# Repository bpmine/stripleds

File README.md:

# stripleds
Projets pour bandeaux de LEDs

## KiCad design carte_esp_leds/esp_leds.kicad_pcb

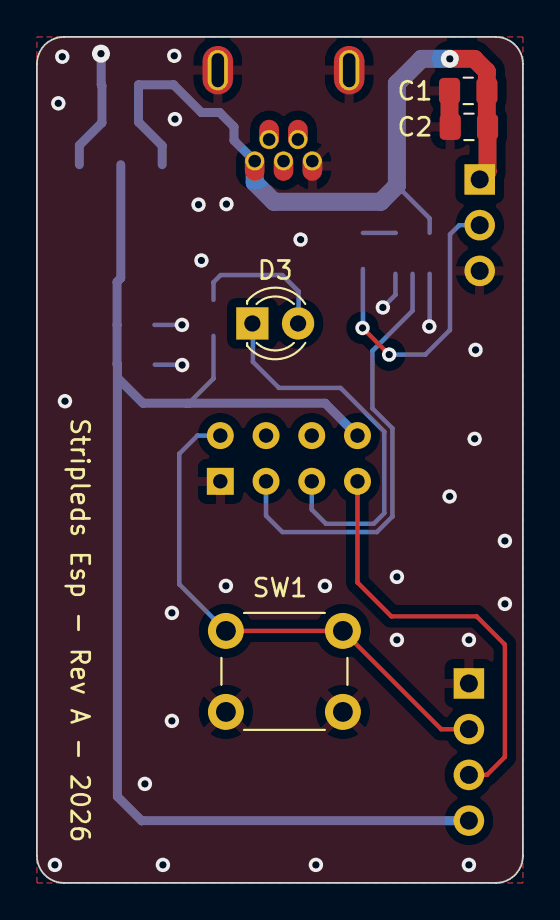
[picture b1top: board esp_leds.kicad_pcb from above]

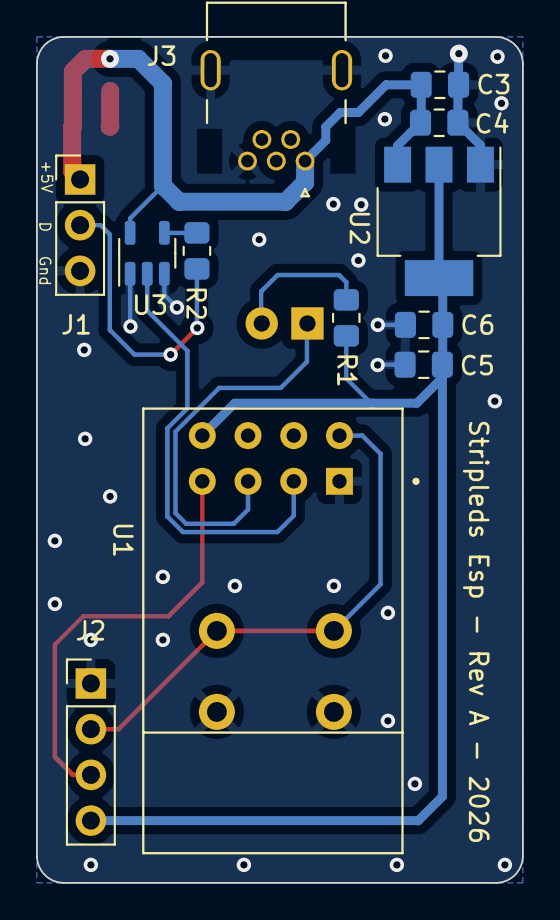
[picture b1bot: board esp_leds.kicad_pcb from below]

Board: 2 copper layers, 27.0 x 47.0 mm, 16 parts (12 on the bottom side), 10 nets.

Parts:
C1, C4, C6: 10n; C_0805_2012Metric_Pad1.18x1.45mm_HandSolder
C2, C3, C5: 1µF; C_0805_2012Metric_Pad1.18x1.45mm_HandSolder
D3: LED; LED_D3.0mm_FlatTop
J1: LEDs; PinHeader_1x03_P2.54mm_Vertical
J2: Prog; PinHeader_1x04_P2.54mm_Vertical
J3: 54819-0519; BPC_MiniUsb_Molex_54819-0519
R1: 220; R_0805_2012Metric_Pad1.20x1.40mm_HandSolder
R2: 100; R_0805_2012Metric_Pad1.20x1.40mm_HandSolder
SW1: SW_Push; SW_PUSH_6mm
U1: BPC_ESP8266-01_ESP-01; BPC_XCVR_ESP8266-01_ESP-01
U2: AMS1117-3.3; SOT-223-3_TabPin2
U3: 74AHCT1G125; SOT-23-5

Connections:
+3.3V: C5.2, C6.1, J2.4, R1.2, U1.8 (VCC), U2.2 (VO)
+5V: C1.2, C2.1, C3.2, C4.1, J1.1, J3.1 (VBUS), J3.6 (VBUS), U2.3 (VI), U3.5 (VCC)
DATA: U1.2 (IO2), U3.2
GND: C1.1, C2.2, C3.1, C4.2, C5.1, C6.2, J1.3, J2.1, J3.5 (GND), J3.10 (GND), J3.11 (SHIELD), J3.12 (SHIELD), J3.S1 (SHIELD), J3.S2 (SHIELD), SW1.2, U1.1 (GND), U2.1 (GND), U3.1, U3.3 (GND)
unnamed: D3.2 (A), R1.1
unnamed: D3.1 (K), U1.3 (IO0)
unnamed: J1.2, R2.1
unnamed: J2.2, SW1.1, U1.5 (TXD)
unnamed: J2.3, U1.4 (RXD)
unnamed: R2.2, U3.4

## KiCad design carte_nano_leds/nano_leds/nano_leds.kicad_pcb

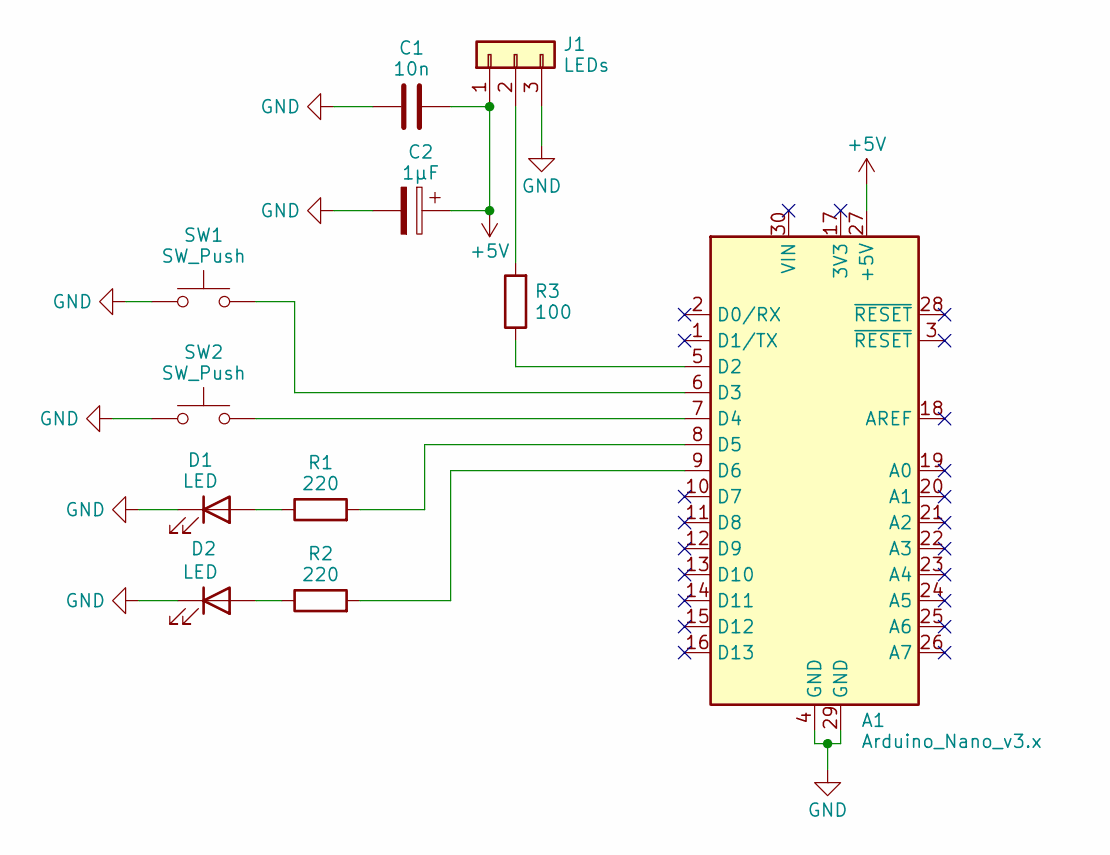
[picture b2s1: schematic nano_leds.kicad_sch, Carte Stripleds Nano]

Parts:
A1: Arduino_Nano_v3.x; BPC_Arduino_Nano
C1: 10n; C_0805_2012Metric_Pad1.18x1.45mm_HandSolder
C2: 1µF; C_0805_2012Metric_Pad1.18x1.45mm_HandSolder
D1, D2: LED; LED_D3.0mm_FlatTop
J1: LEDs; PinHeader_1x03_P2.54mm_Vertical
R1, R2: 220; R_0805_2012Metric_Pad1.20x1.40mm_HandSolder
R3: 100; R_0805_2012Metric_Pad1.20x1.40mm_HandSolder
SW1, SW2: SW_Push; SW_PUSH_6mm

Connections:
+5V: A1.27 (+5V), C1.2, C2.1, J1.1
GND: A1.4 (GND), A1.29 (GND), C1.1, C2.2, D1.1 (K), D2.1 (K), J1.3, SW1.1, SW2.1
unnamed: A1.5 (D2), R3.1
unnamed: A1.6 (D3), SW1.2
unnamed: A1.7 (D4), SW2.2
unnamed: A1.8 (D5), R1.2
unnamed: A1.9 (D6), R2.2
unnamed: D1.2 (A), R1.1
unnamed: D2.2 (A), R2.1
unnamed: J1.2, R3.2

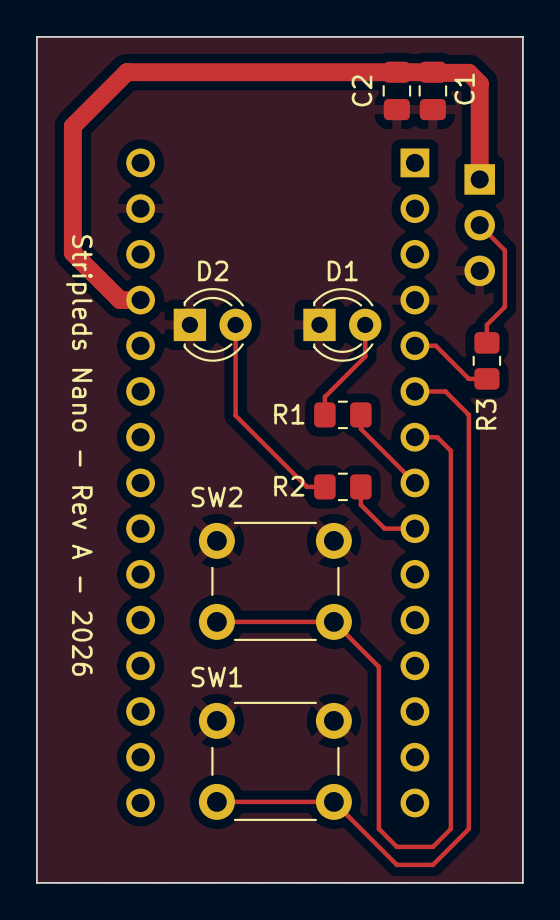
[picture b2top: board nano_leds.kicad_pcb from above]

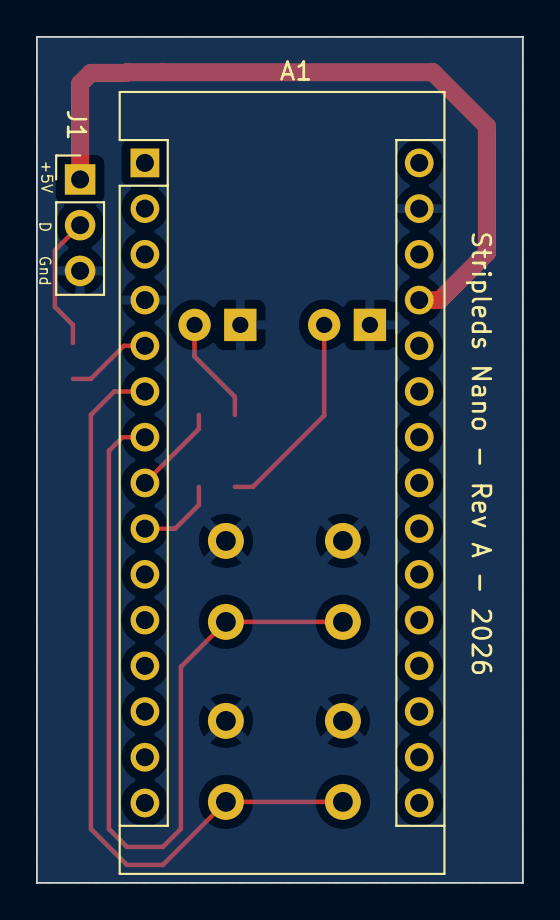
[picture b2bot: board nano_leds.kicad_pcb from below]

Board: 2 copper layers, 27.0 x 47.0 mm, 11 parts (2 on the bottom side), 10 nets.

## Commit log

2025-12-13 Création de la carte
2025-12-13 Schéma
2025-12-14 Création carte strip LEDs basée sur ESP
2025-12-27 Finalisation
